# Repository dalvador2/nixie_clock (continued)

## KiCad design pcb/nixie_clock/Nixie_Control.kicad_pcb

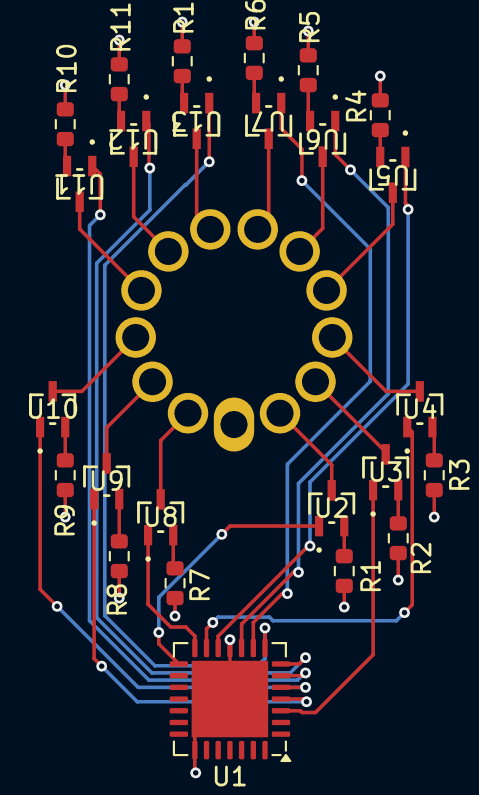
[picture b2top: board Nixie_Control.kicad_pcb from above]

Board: 6 copper layers, 26 parts (1 on the bottom side), 37 nets.

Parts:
R1, R7: 7K87; R_0603_1608Metric
R2, R3, R4, R5, R6, R8, R9, R10, R11, R12: 1K; R_0603_1608Metric
U1: PCA9685BS; QFN-28-1EP_6x6mm_P0.65mm_EP4.25x4.25mm
U2, U3, U4, U5, U6, U7, U8, U9, U10, U11, U12, U13: MSD42WT1G; SOT-323-3_2P2X1P35_ONS
V1: IN14

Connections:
/Nixie_Block2/Cath_0: U1.3 (LED0), U9.1 (BASE)
/Nixie_Block2/Cath_1: U1.4 (LED1), U3.1 (BASE)
/Nixie_Block2/Cath_2: U1.5 (LED2), U4.1 (BASE)
/Nixie_Block2/Cath_3: U1.6 (LED3), U5.1 (BASE)
/Nixie_Block2/Cath_4: U1.7 (LED4), U6.1 (BASE)
/Nixie_Block2/Cath_5: U1.8 (LED5), U7.1 (BASE)
/Nixie_Block2/Cath_6: U1.9 (LED6), U13.1 (BASE)
/Nixie_Block2/Cath_7: U1.10 (LED7), U12.1 (BASE)
/Nixie_Block2/Cath_8: U1.12 (LED8), U11.1 (BASE)
/Nixie_Block2/Cath_9: U1.13 (LED9), U10.1 (BASE)
/Nixie_Block2/Comma_L: U1.14 (LED10), U2.1 (BASE)
/Nixie_Block2/Comma_R: U1.15 (LED11), U8.1 (BASE)
GND: R1.2, R2.2, R3.2, R4.2, R5.2, R6.2, R7.2, R8.2, R9.2, R10.2, R11.2, R12.2, U1.11 (VSS), U1.22 (EXTCLK), U1.29 (VSS)
unnamed: U2.3 (COLLECTOR), V1.13 (Comma_L)
unnamed: R1.1, U2.2 (EMITTER)
unnamed: U3.3 (COLLECTOR), V1.12 (Cath_1)
unnamed: R2.1, U3.2 (EMITTER)
unnamed: U4.3 (COLLECTOR), V1.11 (Cath_2)
unnamed: R3.1, U4.2 (EMITTER)
unnamed: U5.3 (COLLECTOR), V1.10 (Cath_3)
unnamed: R4.1, U5.2 (EMITTER)
unnamed: U6.3 (COLLECTOR), V1.9 (Cath_4)
unnamed: R5.1, U6.2 (EMITTER)
unnamed: U7.3 (COLLECTOR), V1.8 (Cath_5)
unnamed: R6.1, U7.2 (EMITTER)
unnamed: U8.3 (COLLECTOR), V1.2 (Comma_R)
unnamed: R7.1, U8.2 (EMITTER)
unnamed: U9.3 (COLLECTOR), V1.3 (Cath_0)
unnamed: R8.1, U9.2 (EMITTER)
unnamed: U10.3 (COLLECTOR), V1.4 (Cath_9)
unnamed: R9.1, U10.2 (EMITTER)
unnamed: U11.3 (COLLECTOR), V1.5 (Cath_8)
unnamed: R10.1, U11.2 (EMITTER)
unnamed: U12.3 (COLLECTOR), V1.6 (Cath_7)
unnamed: R11.1, U12.2 (EMITTER)
unnamed: U13.3 (COLLECTOR), V1.7 (Cath_6)
unnamed: R12.1, U13.2 (EMITTER)

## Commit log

2024-09-27 nixie cad add
2024-09-27 initial stages of clock design and parts list creation
2024-10-20 pcb layout nixie tube wiring
2024-10-21 nixie pin changes and more wiring
2024-10-22 remove busses and output stuff
2024-10-29 schematic finalisation, footprint assignment and start on placeing components in layout.
2024-11-01 finalization of schematic (might add fuze on 170v supply) looking at pcb routing now. Decided on 6 layers.
2024-11-02 hierarkical pcb switch and finishing of layout time for final checks need to redo nixie tube layout
2024-11-03 3d models done
2024-11-07 fixing some issues.
2024-11-07 added grounding
2024-11-19 changes and improvements
2024-12-10 final commits before sending to jlc
2025-01-02 pcb final changes or lock files
2025-02-11 pcb changes and breakages need to fix later
2025-02-21 comma and digit display functions fully functional
2025-03-11 now communicating
2025-03-24 fix pcb to correct and first steps on a menu
2025-03-24 updated to kicad9
